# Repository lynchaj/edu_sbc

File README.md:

# Educational Single Board Computer (EduSBC)

> **Status:** Schematics & PCB Layout Initialized (KiCad 9 PCB Created)  
> **Last Updated:** 2026-11-22  
> **Measurement Standard:** Strictly Metric (SI: mm / µm)

EduSBC is an open, through-hole Single Board Computer designed to teach computer fundamentals, digital logic, and microarchitecture to beginners—assuming no prior soldering, digital logic, or assembly programming experience. Students build and bring up the board in stages across six lab sessions, moving from polling-based I/O to hardware interrupt service routines (Z80 Mode 1 / Mode 2) via a dedicated jumper.

## Key Hardware & Toolchain Summary

* **CPU & Clocks:** Z80 CMOS CPU (Z84C00 preferred, DIP-40 socketed) with a 4.0000 MHz canned TTL CPU oscillator and a 1.8432 MHz canned TTL UART oscillator.
* **Memory & Glue Logic:** Fixed 64 KB map (32 KB ROM at `$0000–$7FFF` via a universal 28-pin socket supporting 27C256 EPROM or 28C256 EEPROM, and 32 KB SRAM at `$8000–$FFFF`), decoded with 74HCT glue logic.
* **I/O Interfaces:**
  * **Parallel I/O:** 82C55 / 8255 PPI (DIP-40 socketed) at I/O ports `$00–$03` wired to a 26-pin (13×2) horizontal 2.54 mm box header (`JP_GPIO_PWR` selects `+5V` or `GND` on Pin 26).
  * **Serial I/O:** 16C550 / 16550 UART (DIP-40 socketed) at I/O ports `$08–$0F` with both a DE-9 male RS-232 port (MAX232, 5-wire handshaking) and a 6-pin 2.54 mm TTL header (compatible with DTECH FT232RL 5V cables). *Connect either TTL (`J4`) or RS-232 (`J3`), never both simultaneously.*
* **Power & Reset:** 9–15 VDC barrel jack input (standard 12 VDC / 2 A Qualtek `QAWA-24-12-US01` adapter), SPDT power slide switch, reverse Schottky protection, 7805 linear regulator with heatsink clearance, 3.0 mm green power LED, DS1813-5+ reset supervisor, and 74HCT14 reset inverter.
* **Form Factor & CAD:** 160.000 mm × 100.000 mm Eurocard (2-layer JLCPCB spec), designed in **KiCad 9** on **Debian Linux 13 (amd64)** with **FreeRouting 2.5.0** (Specctra DSN / SES workflow).

## Repository Structure

* `edu_sbc.kicad_pro` / `edu_sbc.kicad_prl` — KiCad 9 project and local settings.
* `edu_sbc.kicad_sch` and `01_*.kicad_sch` – `06_*.kicad_sch` — Hierarchical schematic sheets (`root_schematic_edu_sbc_kicad_sch.md` provides schematic notes).
* `edu_sbc.kicad_pcb` and `edu_sbc-drc.rpt` — 2-layer PCB layout and DRC report.
* `edu_sbc.pretty/` and `fp-lib-table` — Local footprint library (including `SW_Slide_Power_SPDT.kicad_mod`) and footprint library table.
* `BOM.md` and `BOM.csv` — Bill of materials grouped by lab session and formatted for component ordering.
* `DESIGN_DECISIONS.md` — Detailed hardware specifications, drafting/routing rules, lab build sequence, and session change log.
* `TO_DO.md` and `LICENSE` — Active task checklist and repository license.

## Getting Started & Workflow

1. Review `DESIGN_DECISIONS.md` for architecture constraints, metric design rules, and the six-lab progressive assembly plan.
2. Check `TO_DO.md` for current schematic, layout, BOM, and verification tasks.
3. Keep project files and datasheets stored locally in your working directory (default local workspace: `/home/lynchaj/Documents/edu_sbc`).
```[cite: 1, 2, 3]

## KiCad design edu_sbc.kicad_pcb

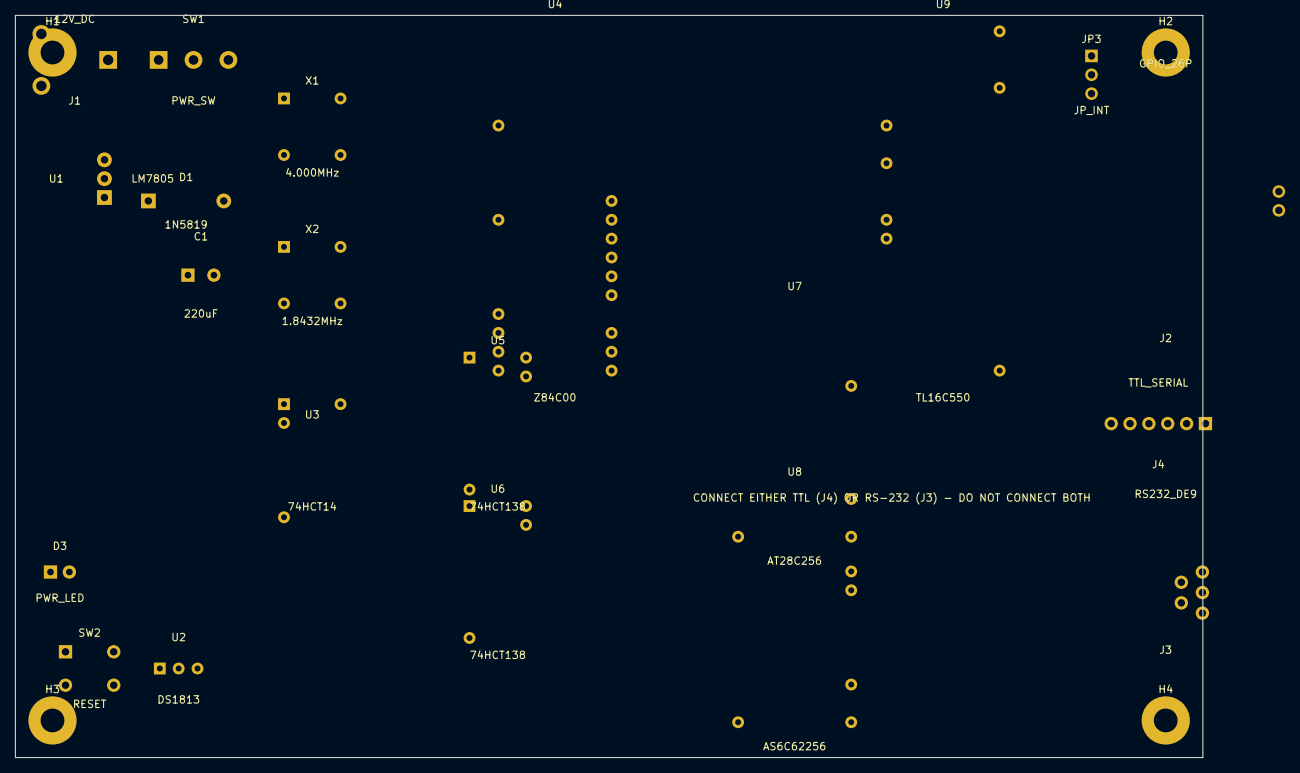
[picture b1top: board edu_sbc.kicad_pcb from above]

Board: 2 copper layers, 160.0 x 100.0 mm, 25 parts (0 on the bottom side), 15 nets, no tracks yet.

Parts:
C1: 220uF; CP_Radial_D8.0mm_P3.50mm
D1: 1N5819; D_DO-41_SOD81_P10.16mm_Horizontal
D3: PWR_LED; LED_D3.0mm
H1, H2, H3, H4: M3_Hole; MountingHole_3.2mm_M3_ISO7380
J1: 12V_DC; BarrelJack_Horizontal
J2: GPIO_26P; IDC-Header_2x13_P2.54mm_Horizontal
J3: RS232_DE9; DSUB-9_Male_Horizontal_P2.77x2.84mm_EdgePinOffset4.94mm_Hou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
J4: TTL_SERIAL; PinHeader_1x06_P2.54mm_Horizontal
JP3: JP_INT; PinHeader_1x03_P2.54mm_Vertical
SW1: PWR_SW; SW_Slide_Power_SPDT
SW2: RESET; SW_PUSH_6mm_H5mm
U1: LM7805; TO-220-3_Vertical
U2: DS1813; TO-92_Inline
U3: 74HCT14; DIP-14_W7.62mm
U4: Z84C00; DIP-40_W15.24mm
U5, U6: 74HCT138; DIP-16_W7.62mm
U7: AT28C256; DIP-28_W15.24mm
U8: AS6C62256; DIP-28_W15.24mm
U9: TL16C550; DIP-40_W15.24mm
X1: 4.000MHz; Oscillator_DIP-8
X2: 1.8432MHz; Oscillator_DIP-8

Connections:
+5V: D3.1, J2.26, J4.3, JP3.2, U1.3, U2.2, U3.14, U4.11, U5.16, U6.16, U7.28, U8.28, U9.40, X1.1, X1.8, X2.1, X2.8
CPU_CLK: U4.6, X1.5
GND: C1.2, D3.2, J1.2, J1.3, J2.25, J3.5, J4.1, JP3.3, SW2.1, SW2.3, U1.2, U2.3, U3.7, U4.29, U5.8, U6.8, U7.14, U8.14, U9.20, X1.4, X2.4
RESET_HIGH: U3.2, U9.35
RXD_TTL: J4.5, U9.10
TXD_TTL: J4.4, U9.11
UART_CLK: U9.16, X2.5
V_IN_RAW: J1.1, SW1.1
V_PROT: C1.1, D1.1, D1.2, SW1.2, U1.1
nINT: JP3.1, U4.16
nIORQ: U4.20, U5.1, U6.1
nRD: U4.21, U7.22, U8.22
nRESET: SW2.2, SW2.4, U2.1, U3.1, U4.26
nUART_CS: U5.15, U9.14
nWR: U4.22, U8.27
